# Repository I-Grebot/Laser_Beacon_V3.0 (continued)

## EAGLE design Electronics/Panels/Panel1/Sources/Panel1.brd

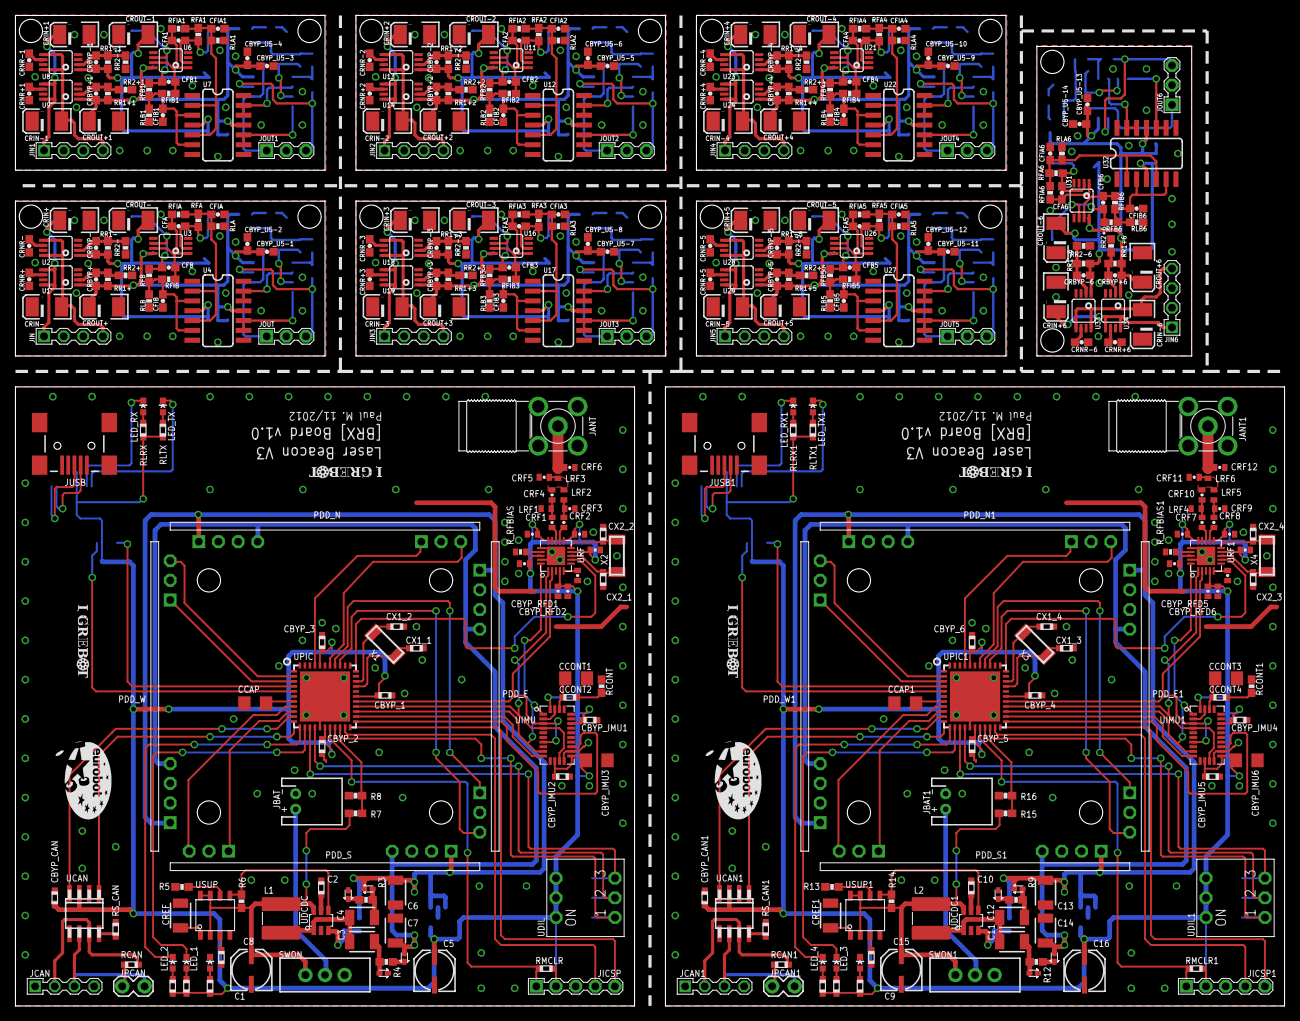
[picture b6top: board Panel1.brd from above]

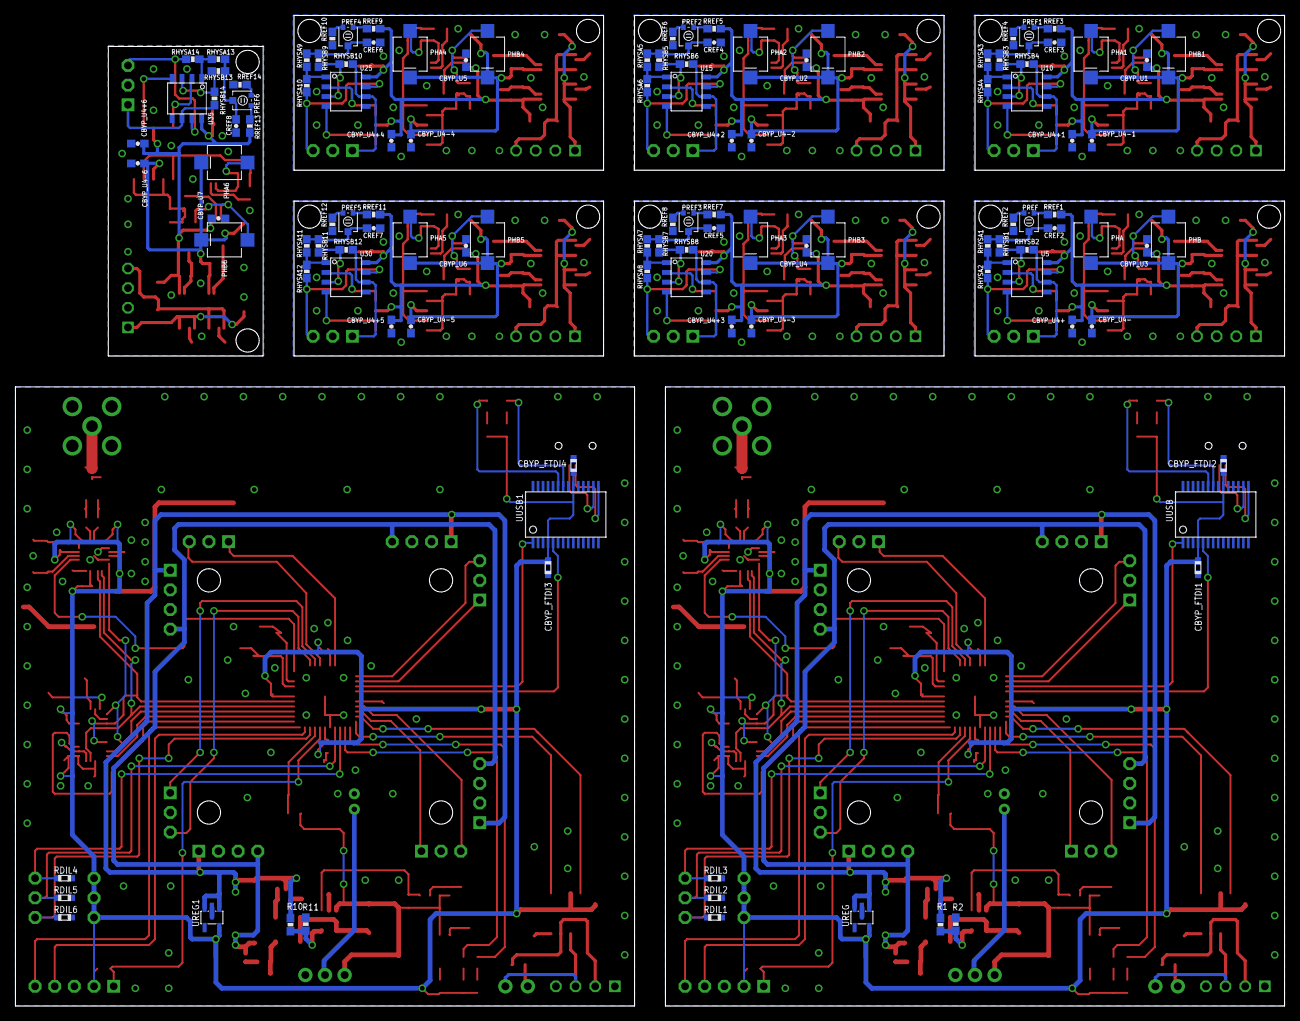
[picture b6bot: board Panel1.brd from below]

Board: 2 copper layers, 164.0 x 128.0 mm, 502 parts (116 on the bottom side), 312 nets.

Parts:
C1, C9: 4.7uF; PANASONIC_C
C2, C10: 47nF_16V; R0603
C3, C4, C11, C12: 1uF_16V; 1210
C5, C16: 10uF; PANASONIC_C
C6, C7, C13, C14: 2.2uF_16V; 1210
C8, C15: 470nF; R0603
CBYP_1, CBYP_2, CBYP_3, CBYP_4, CBYP_5, CBYP_6: 100nF_6.3V; R0603
CBYP_CAN, CBYP_CAN1: 100nF_6.3V; R0603
CBYP_FTDI1, CBYP_FTDI2, CBYP_FTDI3, CBYP_FTDI4: 100nF_6.3V; R0603
CBYP_IMU1, CBYP_IMU2, CBYP_IMU4, CBYP_IMU5: 100nF_6.3V; R0603
CBYP_IMU3, CBYP_IMU6: 10uF_6.3V; 1206
CBYP_RFA1, CBYP_RFA2, CBYP_RFA5, CBYP_RFA6: 100nF_X5R; 0402-CAP
CBYP_RFA3, CBYP_RFA4, CBYP_RFA7, CBYP_RFA8: 220pF_X7R; 0402-CAP
CBYP_RFD1, CBYP_RFD3, CBYP_RFD4, CBYP_RFD5: 100nF_X5R; 0402-CAP
CBYP_RFD2, CBYP_RFD6: 220pF_X7R; 0402-CAP
CBYP_U1, CBYP_U2, CBYP_U3, CBYP_U4, CBYP_U4+, CBYP_U4+1, CBYP_U4+2, CBYP_U4+3, CBYP_U4+4, CBYP_U4+5, CBYP_U4+6, CBYP_U4-, CBYP_U4-1, CBYP_U4-2, CBYP_U4-3, CBYP_U4-4, CBYP_U4-5, CBYP_U4-6, CBYP_U5, CBYP_U5-1, CBYP_U5-3, CBYP_U5-5, CBYP_U5-7, CBYP_U5-9, CBYP_U5-11, CBYP_U5-13, CBYP_U6, CBYP_U7: 1uF; 0603-CAP
CBYP_U5-2, CBYP_U5-4, CBYP_U5-6, CBYP_U5-8, CBYP_U5-10, CBYP_U5-12, CBYP_U5-14: 100nF; 0603-CAP
CCAP, CCAP1: 10uF_6.3V; 1206
CCONT1, CCONT3: 10nF; 1206
CCONT2, CCONT4: 470nF; R0603
CFA, CFA1, CFA2, CFA3, CFA4, CFA5, CFA6: 33pF; 0603-CAP
CFB, CFB1, CFB2, CFB3, CFB4, CFB5, CFB6: 33pF; 0603-CAP
CFIA, CFIA1, CFIA2, CFIA3, CFIA4, CFIA5, CFIA6: 100nF; 0603-CAP
CFIB, CFIB1, CFIB2, CFIB3, CFIB4, CFIB5, CFIB6: 100nF; 0603-CAP
CRBYP+, CRBYP+1, CRBYP+2, CRBYP+3, CRBYP+4, CRBYP+5, CRBYP+6: 10nF; 0603-CAP
CRBYP-, CRBYP-1, CRBYP-2, CRBYP-3, CRBYP-4, CRBYP-5, CRBYP-6: 10nF; 0603-CAP
CREF, CREF1: 1uF; 1210
CREF2, CREF3, CREF4, CREF5, CREF6, CREF7, CREF8: 470nF; 0603-CAP
CRF1, CRF2, CRF7, CRF8: 100pF_NP0; 0402-CAP
CRF3, CRF4, CRF9, CRF10: 1.0pF_NP0; 0402-CAP
CRF5, CRF11: 1.8pF_NP0; 0402-CAP
CRF6, CRF12: 1.5pF_NP0; 0402-CAP
CRIN+, CRIN+1, CRIN+2, CRIN+3, CRIN+4, CRIN+5, CRIN+6: 10uF; EIA3528-KIT
CRIN-, CRIN-1, CRIN-2, CRIN-3, CRIN-4, CRIN-5, CRIN-6: 10uF; EIA3528-KIT
CRNR+, CRNR+1, CRNR+2, CRNR+3, CRNR+4, CRNR+5, CRNR+6: 10nF; 0603-CAP
CRNR-, CRNR-1, CRNR-2, CRNR-3, CRNR-4, CRNR-5, CRNR-6: 10nF; 0603-CAP
CROUT+, CROUT+1, CROUT+2, CROUT+3, CROUT+4, CROUT+5, CROUT+6: 10uF; EIA3528-KIT
CROUT-, CROUT-1, CROUT-2, CROUT-3, CROUT-4, CROUT-5, CROUT-6: 10uF; EIA3528-KIT
CX1_1, CX1_2, CX1_3, CX1_4, CX2_1, CX2_2, CX2_3, CX2_4: 22pF_6.3V; R0603
D1, D2, D3, D4, D5, D6, D7, D8: PMEG2005; SOD-523
JANT, JANT1: ENG_CD_1814400_C1; SMA-PCB-ANGLE
JBAT, JBAT1: JST-2-PTH
JCAN, JCAN1: SIL4; CON4-2.54
JICSP, JICSP1: SIL5; CON5-2.54
JIN, JIN1, JIN2, JIN3, JIN4, JIN5, JIN6: SIL4; CON4-2.54
JOUT, JOUT1, JOUT2, JOUT3, JOUT4, JOUT5, JOUT6: SIL3; CON3-2.54
JPCAN, JPCAN1: 1X02_LOCK
JUSB, JUSB1: USBSMD; USB-MINIB
L1, L2: 10uH; L-5X5
LED_1, LED_2, LED_3, LED_4: LED-0603
LED_POW, LED_POW1: LED-0603
LED_RX, LED_RX1: LED-0603
LED_TX, LED_TX1: LED-0603
LRF1, LRF2, LRF3, LRF4, LRF5, LRF6: 1.2nH; C0402
PDD_E, PDD_E1: PDD_BOARD; PDD_SOCKET
PDD_N, PDD_N1: PDD_BOARD; PDD_SOCKET
PDD_S, PDD_S1: PDD_BOARD; PDD_SOCKET
PDD_W, PDD_W1: PDD_BOARD; PDD_SOCKET
PHA, PHA1, PHA2, PHA3, PHA4, PHA5, PHA6: VBPW34SR
PHB, PHB1, PHB2, PHB3, PHB4, PHB5, PHB6: VBPW34SR
PREF, PREF1, PREF2, PREF3, PREF4, PREF5, PREF6: 100k; TRIM-PVZ2A
R1, R10: 113k; 0603-RES
R2, R11: 13.3k; 0603-RES
R3, R4, R9, R12: 1; 0603-RES
R5, R6, R8, R13, R14, R16: 10k; 0603-RES
R7, R15: 20k; 0603-RES
RCAN, RCAN1: 100; R0603
RCONT, RCONT1: 10k; 0603-RES
RDIL1, RDIL2, RDIL3, RDIL4, RDIL5, RDIL6: 10k; R0603
RFA, RFA1, RFA2, RFA3, RFA4, RFA5, RFA6: 20k; 0603-RES
RFB, RFB1, RFB2, RFB3, RFB4, RFB5, RFB6: 20k; 0603-RES
RFIA, RFIA1, RFIA2, RFIA3, RFIA4, RFIA5, RFIA6: 100; 0603-RES
RFIB, RFIB1, RFIB2, RFIB3, RFIB4, RFIB5, RFIB6: 100; 0603-RES
RHYSA1, RHYSA3, RHYSA5, RHYSA7, RHYSA9, RHYSA11, RHYSA13: 100; 0603-RES
RHYSA2, RHYSA4, RHYSA6, RHYSA8, RHYSA10, RHYSA12, RHYSA14: 10k; 0603-RES
RHYSB1, RHYSB3, RHYSB5, RHYSB7, RHYSB9, RHYSB11, RHYSB13: 100; 0603-RES
RHYSB2, RHYSB4, RHYSB6, RHYSB8, RHYSB10, RHYSB12, RHYSB14: 10k; 0603-RES
RL1, RL2, RL3, RL4: 270; R0603
RLA, RLA1, RLA2, RLA3, RLA4, RLA5, RLA6: 100k; 0603-RES
RLB, RLB1, RLB2, RLB3, RLB4, RLB5, RLB6: 100k; 0603-RES
RLPOW, RLPOW1: 270; R0603
RLRX, RLRX1: 270; R0603
RLTX, RLTX1: 270; R0603
RMCLR, RMCLR1: 4.7k; R0603
RR1+, RR1+1, RR1+2, RR1+3, RR1+4, RR1+5, RR1+6, RR1-, RR1-1, RR1-2, RR1-3, RR1-4, RR1-5, RR1-6: 31.6k; 0603-RES
RR2+, RR2+1, RR2+2, RR2+3, RR2+4, RR2+5, RR2+6, RR2-, RR2-1, RR2-2, RR2-3, RR2-4, RR2-5, RR2-6: 10k; 0603-RES
RREF1, RREF2, RREF3, RREF4, RREF5, RREF6, RREF7, RREF8, RREF9, RREF10, RREF11, RREF12, RREF13, RREF14: 100; 0603-RES
RS_CAN, RS_CAN1: 10k; R0603
R_RFBIAS, R_RFBIAS1: 56k; 0402-RES
SWON, SWON1: SWITCH-SPDT
U1, U9, U14, U19, U24, U29, U34: TPS7A4901NO_PAD; MSOP8
U2, U8, U13, U18, U23, U28, U33: TPS7A3001NO_PAD; MSOP8
U3, U6, U11, U16, U21, U26, U31: OPA2380; MSOP8
U4, U7, U12, U17, U22, U27, U32: INA2143; SOIC14
U5, U10, U15, U20, U25, U30, U35: TLV3502; SOIC8
U$1, U$4, U$5, U$9: LOGOIGREBOT; LOGO_IGREBOT
U$2, U$3: LOGOEUROBOT; LOGO_EUROBOT_1
UCAN, UCAN1: MCP2551; SO-08
UDCDC, UDCDC1: LT3467A; TSOT-23
UDIL, UDIL1: A6E-3104; SW_DIP-3
UIMU, UIMU1: LSM330DL; LLGA-28
UPIC, UPIC1: DSPIC33FJ128MC804_QFN; QFN44-8X8
UREG, UREG1: MCP1801; SOT23-5L
URF, URF1: CC2500; QFN20-0.5
USUP, USUP1: TL7709AC; SOIC8
UUSB, UUSB1: FT232RL-BASICSSOP; SSOP28DB
X1, X3: 8MHz; XTAL_4.9-1.8
X2, X4: 26MHz; XTAL_4.9-1.8

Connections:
3.3V: C5.+, CBYP_1.1, CBYP_2.1, CBYP_3.1, CBYP_CAN.1, CBYP_FTDI1.1, CBYP_FTDI2.1, CBYP_IMU1.1, CBYP_IMU2.1, CBYP_IMU3.1, CBYP_RFA1.2, CBYP_RFA2.2, CBYP_RFA3.2, CBYP_RFA4.2, CBYP_RFD1.2, CBYP_RFD2.2, JICSP.2, RL1.1, RL2.1, RLPOW.1, RLRX.1, RLTX.1, RMCLR.1, UCAN.3, UDIL.1A, UDIL.2A, UDIL.3A, UIMU.12, UIMU.15, UIMU.22, UIMU.28, UPIC.P$17, UPIC.P$28, UPIC.P$40, UREG.5, URF.4, URF.9, URF.11, URF.14, URF.15, URF.18, UUSB.4, UUSB.20
3.3V1: C16.+, CBYP_4.1, CBYP_5.1, CBYP_6.1, CBYP_CAN1.1, CBYP_FTDI3.1, CBYP_FTDI4.1, CBYP_IMU4.1, CBYP_IMU5.1, CBYP_IMU6.1, CBYP_RFA5.2, CBYP_RFA6.2, CBYP_RFA7.2, CBYP_RFA8.2, CBYP_RFD5.2, CBYP_RFD6.2, JICSP1.2, RL3.1, RL4.1, RLPOW1.1, RLRX1.1, RLTX1.1, RMCLR1.1, UCAN1.3, UDIL1.1A, UDIL1.2A, UDIL1.3A, UIMU1.12, UIMU1.15, UIMU1.22, UIMU1.28, UPIC1.P$17, UPIC1.P$28, UPIC1.P$40, UREG1.5, URF1.4, URF1.9, URF1.11, URF1.14, URF1.15, URF1.18, UUSB1.4, UUSB1.20
!CMP_A-B!: JOUT.1, RHYSB2.2, U5.6
!CMP_A-B!1: JOUT1.1, RHYSB4.2, U10.6
!CMP_A-B!2: JOUT2.1, RHYSB6.2, U15.6
!CMP_A-B!3: JOUT3.1, RHYSB8.2, U20.6
!CMP_A-B!4: JOUT4.1, RHYSB10.2, U25.6
!CMP_A-B!5: JOUT5.1, RHYSB12.2, U30.6
!CMP_A-B!6: JOUT6.1, RHYSB14.2, U35.6
!CMP_B-A!: JOUT.3, RHYSA2.2, U5.7
!CMP_B-A!1: JOUT1.3, RHYSA4.2, U10.7
!CMP_B-A!2: JOUT2.3, RHYSA6.2, U15.7
!CMP_B-A!3: JOUT3.3, RHYSA8.2, U20.7
!CMP_B-A!4: JOUT4.3, RHYSA10.2, U25.7
!CMP_B-A!5: JOUT5.3, RHYSA12.2, U30.7
!CMP_B-A!6: JOUT6.3, RHYSA14.2, U35.7
!CSN!_A: UIMU.17, UPIC.P$23
!CSN!_A1: UIMU1.17, UPIC1.P$23
!CSN!_G: UIMU.10, UPIC.P$24
!CSN!_G1: UIMU1.10, UPIC1.P$24
!CSN!_RF: UPIC.P$33, URF.7
!CSN!_RF1: UPIC1.P$33, URF1.7
!MCLR!: JICSP.1, RMCLR.2, UPIC.P$18
!MCLR!1: JICSP1.1, RMCLR1.2, UPIC1.P$18
!SHDN!: R6.2, UDCDC.4, USUP.5
!SHDN!1: R14.2, UDCDC1.4, USUP1.5
+5V: CBYP_U3.1, CBYP_U4+.1, CBYP_U5-1.1, CBYP_U5-2.1, CRBYP+.1, CROUT+.A, RR1+.2, RREF1.1, U1.1, U3.8, U4.11, U5.8
+5V1: CBYP_U1.1, CBYP_U4+1.1, CBYP_U5-3.1, CBYP_U5-4.1, CRBYP+1.1, CROUT+1.A, RR1+1.2, RREF3.1, U6.8, U7.11, U9.1, U10.8
+5V2: CBYP_U2.1, CBYP_U4+2.1, CBYP_U5-5.1, CBYP_U5-6.1, CRBYP+2.1, CROUT+2.A, RR1+2.2, RREF5.1, U11.8, U12.11, U14.1, U15.8
+5V3: CBYP_U4.1, CBYP_U4+3.1, CBYP_U5-7.1, CBYP_U5-8.1, CRBYP+3.1, CROUT+3.A, RR1+3.2, RREF7.1, U16.8, U17.11, U19.1, U20.8
+5V4: CBYP_U4+4.1, CBYP_U5.1, CBYP_U5-9.1, CBYP_U5-10.1, CRBYP+4.1, CROUT+4.A, RR1+4.2, RREF9.1, U21.8, U22.11, U24.1, U25.8
+5V5: CBYP_U4+5.1, CBYP_U5-11.1, CBYP_U5-12.1, CBYP_U6.1, CRBYP+5.1, CROUT+5.A, RR1+5.2, RREF11.1, U26.8, U27.11, U29.1, U30.8
+5V6: CBYP_U4+6.1, CBYP_U5-13.1, CBYP_U5-14.1, CBYP_U7.1, CRBYP+6.1, CROUT+6.A, RR1+6.2, RREF13.1, U31.8, U32.11, U34.1, U35.8
+12V: C6.1, D1.C, PDD_E.1, PDD_N.1, PDD_S.1, PDD_W.1, R1.2, UREG.1, UREG.3
+12V1: C13.1, D5.C, PDD_E1.1, PDD_N1.1, PDD_S1.1, PDD_W1.1, R10.2, UREG1.1, UREG1.3
-5V: CBYP_U4-.2, CRBYP-.1, CROUT-.C, PHA.A, PHB.A, RR1-.2, U2.1, U4.4
-5V1: CBYP_U4-1.2, CRBYP-1.1, CROUT-1.C, PHA1.A, PHB1.A, RR1-1.2, U7.4, U8.1
-5V2: CBYP_U4-2.2, CRBYP-2.1, CROUT-2.C, PHA2.A, PHB2.A, RR1-2.2, U12.4, U13.1
-5V3: CBYP_U4-3.2, CRBYP-3.1, CROUT-3.C, PHA3.A, PHB3.A, RR1-3.2, U17.4, U18.1
-5V4: CBYP_U4-4.2, CRBYP-4.1, CROUT-4.C, PHA4.A, PHB4.A, RR1-4.2, U22.4, U23.1
-5V5: CBYP_U4-5.2, CRBYP-5.1, CROUT-5.C, PHA5.A, PHB5.A, RR1-5.2, U27.4, U28.1
-5V6: CBYP_U4-6.2, CRBYP-6.1, CROUT-6.C, PHA6.A, PHB6.A, RR1-6.2, U32.4, U33.1
-12V: C7.1, D4.A, PDD_E.4, PDD_N.4, PDD_S.4, PDD_W.4
-12V1: C14.1, D8.A, PDD_E1.4, PDD_N1.4, PDD_S1.4, PDD_W1.4
AGND: CBYP_U3.2, CBYP_U4+.2, CBYP_U4-.1, CBYP_U5-1.2, CBYP_U5-2.2, CFIA.2, CFIB.2, CREF2.2, CRIN+.C, CRIN-.A, CRNR+.2, CRNR-.2, CROUT+.C, CROUT-.A, JIN.2, JIN.3, JOUT.2, RLA.1, RLB.1, RR2+.1, RR2-.1, RREF2.1, U1.4, U2.4, U3.3, U3.4, U3.5, U4.8, U4.14, U5.5
AGND1: CBYP_U1.2, CBYP_U4+1.2, CBYP_U4-1.1, CBYP_U5-3.2, CBYP_U5-4.2, CFIA1.2, CFIB1.2, CREF3.2, CRIN+1.C, CRIN-1.A, CRNR+1.2, CRNR-1.2, CROUT+1.C, CROUT-1.A, JIN1.2, JIN1.3, JOUT1.2, RLA1.1, RLB1.1, RR2+1.1, RR2-1.1, RREF4.1, U6.3, U6.4, U6.5, U7.8, U7.14, U8.4, U9.4, U10.5
AGND2: CBYP_U2.2, CBYP_U4+2.2, CBYP_U4-2.1, CBYP_U5-5.2, CBYP_U5-6.2, CFIA2.2, CFIB2.2, CREF4.2, CRIN+2.C, CRIN-2.A, CRNR+2.2, CRNR-2.2, CROUT+2.C, CROUT-2.A, JIN2.2, JIN2.3, JOUT2.2, RLA2.1, RLB2.1, RR2+2.1, RR2-2.1, RREF6.1, U11.3, U11.4, U11.5, U12.8, U12.14, U13.4, U14.4, U15.5
AGND3: CBYP_U4.2, CBYP_U4+3.2, CBYP_U4-3.1, CBYP_U5-7.2, CBYP_U5-8.2, CFIA3.2, CFIB3.2, CREF5.2, CRIN+3.C, CRIN-3.A, CRNR+3.2, CRNR-3.2, CROUT+3.C, CROUT-3.A, JIN3.2, JIN3.3, JOUT3.2, RLA3.1, RLB3.1, RR2+3.1, RR2-3.1, RREF8.1, U16.3, U16.4, U16.5, U17.8, U17.14, U18.4, U19.4, U20.5
AGND4: CBYP_U4+4.2, CBYP_U4-4.1, CBYP_U5.2, CBYP_U5-9.2, CBYP_U5-10.2, CFIA4.2, CFIB4.2, CREF6.2, CRIN+4.C, CRIN-4.A, CRNR+4.2, CRNR-4.2, CROUT+4.C, CROUT-4.A, JIN4.2, JIN4.3, JOUT4.2, RLA4.1, RLB4.1, RR2+4.1, RR2-4.1, RREF10.1, U21.3, U21.4, U21.5, U22.8, U22.14, U23.4, U24.4, U25.5
AGND5: CBYP_U4+5.2, CBYP_U4-5.1, CBYP_U5-11.2, CBYP_U5-12.2, CBYP_U6.2, CFIA5.2, CFIB5.2, CREF7.2, CRIN+5.C, CRIN-5.A, CRNR+5.2, CRNR-5.2, CROUT+5.C, CROUT-5.A, JIN5.2, JIN5.3, JOUT5.2, RLA5.1, RLB5.1, RR2+5.1, RR2-5.1, RREF12.1, U26.3, U26.4, U26.5, U27.8, U27.14, U28.4, U29.4, U30.5
AGND6: CBYP_U4+6.2, CBYP_U4-6.1, CBYP_U5-13.2, CBYP_U5-14.2, CBYP_U7.2, CFIA6.2, CFIB6.2, CREF8.2, CRIN+6.C, CRIN-6.A, CRNR+6.2, CRNR-6.2, CROUT+6.C, CROUT-6.A, JIN6.2, JIN6.3, JOUT6.2, RLA6.1, RLB6.1, RR2+6.1, RR2-6.1, RREF14.1, U31.3, U31.4, U31.5, U32.8, U32.14, U33.4, U34.4, U35.5
CANH: JCAN.2, RCAN.1, UCAN.7
CANH1: JCAN1.2, RCAN1.1, UCAN1.7
CANL: JCAN.3, JPCAN.2, UCAN.6
CANL1: JCAN1.3, JPCAN1.2, UCAN1.6
CAN_RX: UCAN.4, UPIC.P$10
CAN_RX1: UCAN1.4, UPIC1.P$10
CAN_TX: UCAN.1, UPIC.P$11
CAN_TX1: UCAN1.1, UPIC1.P$11
DIL1: RDIL1.1, UDIL.1B, UPIC.P$20
DIL2: RDIL2.1, UDIL.2B, UPIC.P$15
DIL3: RDIL3.1, UDIL.3B, UPIC.P$14
DIL4: RDIL4.1, UDIL1.3B, UPIC1.P$14
DIL5: RDIL5.1, UDIL1.2B, UPIC1.P$15
DIL6: RDIL6.1, UDIL1.1B, UPIC1.P$20
E_!A-B!: PDD_E.5, UPIC.P$37
E_!A-B!1: PDD_E1.5, UPIC1.P$37
E_!B-A!: PDD_E.7, UPIC.P$36
E_!B-A!1: PDD_E1.7, UPIC1.P$36
GND: C1.-, C2.2, C5.-, C6.2, C7.2, C8.2, CBYP_1.2, CBYP_2.2, CBYP_3.2, CBYP_CAN.2, CBYP_FTDI1.2, CBYP_FTDI2.2, CBYP_IMU1.2, CBYP_IMU2.2, CBYP_IMU3.2, CBYP_RFA1.1, CBYP_RFA2.1, CBYP_RFA3.1, CBYP_RFA4.1, CBYP_RFD1.1, CBYP_RFD2.1, CBYP_RFD3.1, CCAP.2, CCONT1.2, CREF.1, CRF3.1, CRF5.1, CRF6.1, CX1_1.2, CX1_2.2, CX2_1.2, CX2_2.2, D2.A, D3.C, JANT.B1, JANT.B2, JANT.B3, JANT.B4, JBAT.1, JCAN.1, JCAN.4, JICSP.3, JUSB.GND, LED_POW.C, LRF1.1, PDD_E.2, PDD_E.3, PDD_E.6, PDD_N.2, PDD_N.3, PDD_N.6, PDD_S.2, PDD_S.3, PDD_S.6, PDD_W.2, PDD_W.3, PDD_W.6, R2.1, R5.1, R8.1, RCONT.1, RDIL1.2, RDIL2.2, RDIL3.2, RS_CAN.1, R_RFBIAS.2, UCAN.2, UDCDC.2, UIMU.2, UIMU.11, UIMU.14, UIMU.16, UIMU.18, UIMU.19, UIMU.20, UIMU.23, UIMU.24, UIMU.25, UIMU.27, UPIC.P$6, UPIC.P$16, UPIC.P$29, UPIC.P$39, UPIC.PAD, UREG.2, URF.16, URF.19, URF.PAD, USUP.4, UUSB.7, UUSB.18, UUSB.21, UUSB.25, UUSB.26
GND1: C9.-, C10.2, C13.2, C14.2, C15.2, C16.-, CBYP_4.2, CBYP_5.2, CBYP_6.2, CBYP_CAN1.2, CBYP_FTDI3.2, CBYP_FTDI4.2, CBYP_IMU4.2, CBYP_IMU5.2, CBYP_IMU6.2, CBYP_RFA5.1, CBYP_RFA6.1, CBYP_RFA7.1, CBYP_RFA8.1, CBYP_RFD4.1, CBYP_RFD5.1, CBYP_RFD6.1, CCAP1.2, CCONT3.2, CREF1.1, CRF9.1, CRF11.1, CRF12.1, CX1_3.2, CX1_4.2, CX2_3.2, CX2_4.2, D6.A, D7.C, JANT1.B1, JANT1.B2, JANT1.B3, JANT1.B4, JBAT1.1, JCAN1.1, JCAN1.4, JICSP1.3, JUSB1.GND, LED_POW1.C, LRF4.1, PDD_E1.2, PDD_E1.3, PDD_E1.6, PDD_N1.2, PDD_N1.3, PDD_N1.6, PDD_S1.2, PDD_S1.3, PDD_S1.6, PDD_W1.2, PDD_W1.3, PDD_W1.6, R11.1, R13.1, R16.1, RCONT1.1, RDIL4.2, RDIL5.2, RDIL6.2, RS_CAN1.1, R_RFBIAS1.2, UCAN1.2, UDCDC1.2, UIMU1.2, UIMU1.11, UIMU1.14, UIMU1.16, UIMU1.18, UIMU1.19, UIMU1.20, UIMU1.23, UIMU1.24, UIMU1.25, UIMU1.27, UPIC1.P$6, UPIC1.P$16, UPIC1.P$29, UPIC1.P$39, UPIC1.PAD, UREG1.2, URF1.16, URF1.19, URF1.PAD, USUP1.4, UUSB1.7, UUSB1.18, UUSB1.21, UUSB1.25, UUSB1.26
LED_1: LED_1.C, UPIC.P$13
LED_2: LED_2.C, UPIC.P$12
LED_3: LED_3.C, UPIC1.P$13
LED_4: LED_4.C, UPIC1.P$12
LED_RX: LED_RX.C, UUSB.22
LED_RX1: LED_RX1.C, UUSB1.22
LED_TX: LED_TX.C, UUSB.23
LED_TX1: LED_TX1.C, UUSB1.23
MISO: UIMU.3, UIMU.7, UPIC.P$27, URF.2
MISO1: UIMU1.3, UIMU1.7, UPIC1.P$27, URF1.2
MOSI: UIMU.1, UIMU.9, UPIC.P$25, URF.20
MOSI1: UIMU1.1, UIMU1.9, UPIC1.P$25, URF1.20
unnamed: CRF1.2, CRF4.2, LRF1.2
unnamed: LED_TX.A, RLTX.2
unnamed: CRF2.2, CRF3.2, LRF2.1
unnamed: CRF4.1, CRF5.2, LRF2.2, LRF3.1
unnamed: RS_CAN.2, UCAN.8
unnamed: JPCAN.1, RCAN.2
unnamed: CRF6.2, JANT.A, LRF3.2
unnamed: LED_RX.A, RLRX.2
unnamed: LED_1.A, RL1.2
unnamed: LED_2.A, RL2.2
unnamed: C2.1, UDCDC.5
unnamed: JBAT.2, SWON.2
unnamed: C3.1, C4.1, L1.2, UDCDC.1
unnamed: C3.2, D3.A, R4.2
unnamed: D2.C, R3.1
unnamed: C4.2, D1.A, R3.2
unnamed: R5.2, USUP.6
unnamed: R1.1, R2.2, UDCDC.3
unnamed: D4.C, R4.1
unnamed: CCONT2.2, RCONT.2
unnamed: LED_POW.A, RLPOW.2
unnamed: RS_CAN1.2, UCAN1.8
unnamed: CRF7.2, CRF10.2, LRF4.2
unnamed: CRF8.2, CRF9.2, LRF5.1
unnamed: CRF10.1, CRF11.2, LRF5.2, LRF6.1
unnamed: CRF12.2, JANT1.A, LRF6.2
unnamed: JPCAN1.1, RCAN1.2
unnamed: LED_TX1.A, RLTX1.2
unnamed: LED_RX1.A, RLRX1.2
unnamed: LED_3.A, RL3.2
unnamed: LED_4.A, RL4.2
unnamed: C11.1, C12.1, L2.2, UDCDC1.1
unnamed: C10.1, UDCDC1.5
unnamed: D6.C, R9.1
unnamed: C12.2, D5.A, R9.2
unnamed: D8.C, R12.1
unnamed: C11.2, D7.A, R12.2
unnamed: R10.1, R11.2, UDCDC1.3
unnamed: R13.2, USUP1.6
unnamed: JBAT1.2, SWON1.2
unnamed: CCONT4.2, RCONT1.2
unnamed: LED_POW1.A, RLPOW1.2
unnamed: CRNR+.1, U1.6
unnamed: CRNR-.1, U2.6
unnamed: CRBYP+.2, RR1+.1, RR2+.2, U1.2
unnamed: CRBYP-.2, RR1-.1, RR2-.2, U2.2
unnamed: CFA.2, RFIA.1, U3.1
unnamed: CFA.1, PHA.K, RFA.1, U3.2
unnamed: CFB.2, RFIB.1, U3.7
unnamed: CFB.1, PHB.K, RFB.1, U3.6
unnamed: RHYSA1.2, RHYSA2.1, U5.1
unnamed: RHYSB1.2, RHYSB2.1, U5.3
unnamed: PREF.1, RREF1.2
unnamed: PREF.3, RREF2.2
unnamed: CRNR+1.1, U9.6
unnamed: CRNR-1.1, U8.6
unnamed: CRBYP+1.2, RR1+1.1, RR2+1.2, U9.2
unnamed: CRBYP-1.2, RR1-1.1, RR2-1.2, U8.2
unnamed: CFA1.2, RFIA1.1, U6.1
unnamed: CFA1.1, PHA1.K, RFA1.1, U6.2
unnamed: CFB1.2, RFIB1.1, U6.7
unnamed: CFB1.1, PHB1.K, RFB1.1, U6.6
unnamed: RHYSA3.2, RHYSA4.1, U10.1
unnamed: RHYSB3.2, RHYSB4.1, U10.3
unnamed: PREF1.1, RREF3.2
unnamed: PREF1.3, RREF4.2
unnamed: CRNR+2.1, U14.6
unnamed: CRNR-2.1, U13.6
unnamed: CRBYP+2.2, RR1+2.1, RR2+2.2, U14.2
unnamed: CRBYP-2.2, RR1-2.1, RR2-2.2, U13.2
unnamed: CFA2.2, RFIA2.1, U11.1
unnamed: CFA2.1, PHA2.K, RFA2.1, U11.2
unnamed: CFB2.2, RFIB2.1, U11.7
unnamed: CFB2.1, PHB2.K, RFB2.1, U11.6
unnamed: RHYSA5.2, RHYSA6.1, U15.1
unnamed: RHYSB5.2, RHYSB6.1, U15.3
unnamed: PREF2.1, RREF5.2
unnamed: PREF2.3, RREF6.2
unnamed: CRNR+3.1, U19.6
unnamed: CRNR-3.1, U18.6
unnamed: CRBYP+3.2, RR1+3.1, RR2+3.2, U19.2
unnamed: CRBYP-3.2, RR1-3.1, RR2-3.2, U18.2
unnamed: CFA3.2, RFIA3.1, U16.1
unnamed: CFA3.1, PHA3.K, RFA3.1, U16.2
unnamed: CFB3.2, RFIB3.1, U16.7
unnamed: CFB3.1, PHB3.K, RFB3.1, U16.6
unnamed: RHYSA7.2, RHYSA8.1, U20.1
unnamed: RHYSB7.2, RHYSB8.1, U20.3
unnamed: PREF3.1, RREF7.2
unnamed: PREF3.3, RREF8.2
unnamed: CRNR+4.1, U24.6
unnamed: CRNR-4.1, U23.6
unnamed: CRBYP+4.2, RR1+4.1, RR2+4.2, U24.2
unnamed: CRBYP-4.2, RR1-4.1, RR2-4.2, U23.2
unnamed: CFA4.2, RFIA4.1, U21.1
unnamed: CFA4.1, PHA4.K, RFA4.1, U21.2
unnamed: CFB4.2, RFIB4.1, U21.7
unnamed: CFB4.1, PHB4.K, RFB4.1, U21.6
unnamed: RHYSA9.2, RHYSA10.1, U25.1
unnamed: RHYSB9.2, RHYSB10.1, U25.3
unnamed: PREF4.1, RREF9.2
unnamed: PREF4.3, RREF10.2
unnamed: CRNR+5.1, U29.6
unnamed: CRNR-5.1, U28.6
unnamed: CRBYP+5.2, RR1+5.1, RR2+5.2, U29.2
unnamed: CRBYP-5.2, RR1-5.1, RR2-5.2, U28.2
unnamed: CFA5.2, RFIA5.1, U26.1
unnamed: CFA5.1, PHA5.K, RFA5.1, U26.2
unnamed: CFB5.2, RFIB5.1, U26.7
unnamed: CFB5.1, PHB5.K, RFB5.1, U26.6
unnamed: RHYSA11.2, RHYSA12.1, U30.1
unnamed: RHYSB11.2, RHYSB12.1, U30.3
unnamed: PREF5.1, RREF11.2
unnamed: PREF5.3, RREF12.2
unnamed: CRNR+6.1, U34.6
unnamed: CRNR-6.1, U33.6
unnamed: CRBYP+6.2, RR1+6.1, RR2+6.2, U34.2
unnamed: CRBYP-6.2, RR1-6.1, RR2-6.2, U33.2
unnamed: CFA6.2, RFIA6.1, U31.1
unnamed: CFA6.1, PHA6.K, RFA6.1, U31.2
unnamed: CFB6.2, RFIB6.1, U31.7
unnamed: CFB6.1, PHB6.K, RFB6.1, U31.6
unnamed: RHYSA13.2, RHYSA14.1, U35.1
unnamed: RHYSB13.2, RHYSB14.1, U35.3
unnamed: PREF6.1, RREF13.2
unnamed: PREF6.3, RREF14.2
N_!A-B!: PDD_N.5, UPIC.P$41
N_!A-B!1: PDD_N1.5, UPIC1.P$41
N_!B-A!: PDD_N.7, UPIC.P$38
N_!B-A!1: PDD_N1.7, UPIC1.P$38
PGC: JICSP.5, UPIC.P$22
PGC1: JICSP1.5, UPIC1.P$22
PGD: JICSP.4, UPIC.P$21
PGD1: JICSP1.4, UPIC1.P$21
RF_N: CRF1.1, URF.13
RF_N1: CRF7.1, URF1.13
RF_P: CRF2.1, URF.12
RF_P1: CRF8.1, URF1.12
R_RFBIAS: R_RFBIAS.1, URF.17
R_RFBIAS1: R_RFBIAS1.1, URF1.17
SCLK: UIMU.4, UIMU.13, UPIC.P$26, URF.1
SCLK1: UIMU1.4, UIMU1.13, UPIC1.P$26, URF1.1
SENSE_BAT: R7.2, R8.2, UPIC.P$19
SENSE_BAT1: R15.2, R16.2, UPIC1.P$19
SUB_A-B: U4.9, U4.10, U5.4
SUB_A-B1: U7.9, U7.10, U10.4
SUB_A-B2: U12.9, U12.10, U15.4
SUB_A-B3: U17.9, U17.10, U20.4
SUB_A-B4: U22.9, U22.10, U25.4
SUB_A-B5: U27.9, U27.10, U30.4
SUB_A-B6: U32.9, U32.10, U35.4
SUB_B-A: U4.12, U4.13, U5.2
SUB_B-A1: U7.12, U7.13, U10.2
SUB_B-A2: U12.12, U12.13, U15.2
SUB_B-A3: U17.12, U17.13, U20.2
SUB_B-A4: U22.12, U22.13, U25.2
SUB_B-A5: U27.12, U27.13, U30.2
SUB_B-A6: U32.12, U32.13, U35.2
S_!A-B!: PDD_S.5, UPIC.P$9
S_!A-B!1: PDD_S1.5, UPIC1.P$9
S_!B-A!: PDD_S.7, UPIC.P$8
S_!B-A!1: PDD_S1.7, UPIC1.P$8
TI_A: CFIA.1, RFA.2, RFIA.2, RLA.2, U4.2, U4.5
TI_A1: CFIA1.1, RFA1.2, RFIA1.2, RLA1.2, U7.2, U7.5
TI_A2: CFIA2.1, RFA2.2, RFIA2.2, RLA2.2, U12.2, U12.5
TI_A3: CFIA3.1, RFA3.2, RFIA3.2, RLA3.2, U17.2, U17.5
TI_A4: CFIA4.1, RFA4.2, RFIA4.2, RLA4.2, U22.2, U22.5
TI_A5: CFIA5.1, RFA5.2, RFIA5.2, RLA5.2, U27.2, U27.5
TI_A6: CFIA6.1, RFA6.2, RFIA6.2, RLA6.2, U32.2, U32.5
TI_B: CFIB.1, RFB.2, RFIB.2, RLB.2, U4.3, U4.6
TI_B1: CFIB1.1, RFB1.2, RFIB1.2, RLB1.2, U7.3, U7.6
TI_B2: CFIB2.1, RFB2.2, RFIB2.2, RLB2.2, U12.3, U12.6
TI_B3: CFIB3.1, RFB3.2, RFIB3.2, RLB3.2, U17.3, U17.6
TI_B4: CFIB4.1, RFB4.2, RFIB4.2, RLB4.2, U22.3, U22.6
TI_B5: CFIB5.1, RFB5.2, RFIB5.2, RLB5.2, U27.3, U27.6
TI_B6: CFIB6.1, RFB6.2, RFIB6.2, RLB6.2, U32.3, U32.6
USBDM: JUSB.D-, UUSB.16
USBDM1: JUSB1.D-, UUSB1.16
USBDP: JUSB.D+, UUSB.15
USBDP1: JUSB1.D+, UUSB1.15
USB_RX: UPIC.P$5, UUSB.5
USB_RX1: UPIC1.P$5, UUSB1.5
USB_TX: UPIC.P$4, UUSB.1
USB_TX1: UPIC1.P$4, UUSB1.1
VBAT: C1.+, L1.1, R6.1, R7.1, SWON.1, UDCDC.6, USUP.2, USUP.7, USUP.8
VBAT1: C9.+, L2.1, R14.1, R15.1, SWON1.1, UDCDC1.6, USUP1.2, USUP1.7, USUP1.8
VCAP: CCAP.1, UPIC.P$7
VCAP1: CCAP1.1, UPIC1.P$7
VCONT: CCONT1.1, CCONT2.1, UIMU.26
VCONT1: CCONT3.1, CCONT4.1, UIMU1.26
VCT: C8.1, USUP.3
VCT1: C15.1, USUP1.3
VDCOUPL: CBYP_RFD3.2, URF.5
VDCOUPL1: CBYP_RFD4.2, URF1.5
VIN+: CRIN+.A, JIN.1, U1.5, U1.8
VIN+1: CRIN+1.A, JIN1.1, U9.5, U9.8
VIN+2: CRIN+2.A, JIN2.1, U14.5, U14.8
VIN+3: CRIN+3.A, JIN3.1, U19.5, U19.8
VIN+4: CRIN+4.A, JIN4.1, U24.5, U24.8
VIN+5: CRIN+5.A, JIN5.1, U29.5, U29.8
VIN+6: CRIN+6.A, JIN6.1, U34.5, U34.8
VIN-: CRIN-.C, JIN.4, U2.5, U2.8
VIN-1: CRIN-1.C, JIN1.4, U8.5, U8.8
VIN-2: CRIN-2.C, JIN2.4, U13.5, U13.8
VIN-3: CRIN-3.C, JIN3.4, U18.5, U18.8
VIN-4: CRIN-4.C, JIN4.4, U23.5, U23.8
VIN-5: CRIN-5.C, JIN5.4, U28.5, U28.8
VIN-6: CRIN-6.C, JIN6.4, U33.5, U33.8
VREF: CREF.2, USUP.1
VREF1: CREF1.2, USUP1.1
VREF2: CREF2.1, PREF.2, RHYSA1.1, RHYSB1.1
VREF3: CREF3.1, PREF1.2, RHYSA3.1, RHYSB3.1
VREF4: CREF4.1, PREF2.2, RHYSA5.1, RHYSB5.1
VREF5: CREF5.1, PREF3.2, RHYSA7.1, RHYSB7.1
VREF6: CREF6.1, PREF4.2, RHYSA9.1, RHYSB9.1
VREF7: CREF7.1, PREF5.2, RHYSA11.1, RHYSB11.1
VREF8: CREF8.1, PREF6.2, RHYSA13.1, RHYSB13.1
W_!A-B!: PDD_W.5, UPIC.P$3
W_!A-B!1: PDD_W1.5, UPIC1.P$3
W_!B-A!: PDD_W.7, UPIC.P$2
W_!B-A!1: PDD_W1.7, UPIC1.P$2
X1_OSC1: CX1_1.1, UPIC.P$30, X1.P$1
X1_OSC2: CX1_2.1, UPIC.P$31, X1.P$2
X1_OSC3: CX1_3.1, UPIC1.P$30, X3.P$1
X1_OSC4: CX1_4.1, UPIC1.P$31, X3.P$2
X2_OSC1: CX2_1.1, URF.8, X2.P$1
X2_OSC2: CX2_2.1, URF.10, X2.P$2
X2_OSC3: CX2_3.1, URF1.8, X4.P$1
X2_OSC4: CX2_4.1, URF1.10, X4.P$2

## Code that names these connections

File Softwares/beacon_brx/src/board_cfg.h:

/* -----------------------------------------------------------------------------
 * Beacon [BRX]
 * I-Grebot Laser Beacon V3.0
 * -----------------------------------------------------------------------------
 * File        : board_cfg.h
 * Language    : C
 * Author      : Paul M.
 * Creation    : 2013-03-10
 * -----------------------------------------------------------------------------
 * Description
 *   See main module header file for a full description
 * -----------------------------------------------------------------------------
 * Versionning informations
 * Repository: http://svn2.assembla.com/svn/paranoid_android/
 * -----------------------------------------------------------------------------
 * $Rev:: 877                                                                  $
 * $LastChangedBy:: Paul.M                                                     $
 * $LastChangedDate:: 2013-03-30 23:59:51 +0100 (sam., 30 mars 2013)           $
 * -----------------------------------------------------------------------------
 * Version     Comment                                   Author       Date
 * 1.0         Initial release                           Paul M.      2013-03-10
 * -----------------------------------------------------------------------------
 */

#ifndef _BOARD_H_
#define _BOARD_H_

// Hardware main include
#include <p33Fxxxx.h>

// Compiler related types
typedef unsigned char uint8_t ;
typedef signed   char sint8_t ;
typedef unsigned int  uint16_t;
typedef signed   int  sint16_t;
typedef unsigned long uint32_t;
typedef signed   long sint32_t;

// -----------------------------------------------------------------------------
// FREQUENCIES
// -----------------------------------------------------------------------------

// Primary Oscillator frequency
#define FIN 8000000

// FOSC = (FIN/N1) * M / N2
// N1 = 4, M = 32, N2 = 2
#define PLL_RATIO (32/(4*2))

// Add-up all frequency tunnings
#define FOSC 64000000 // (FIN*PLL_RATIO)
#define FCY  32000000 // (FOSC/2)

#define NCY_FOR_ONE_MS 50000 // rough estimate for 1ms active delay

// -----------------------------------------------------------------------------
// PPS IO MACROS
// -----------------------------------------------------------------------------

#define UNLOCK_PPS {__builtin_write_OSCCONL(OSCCON & 0xBF); \
                    while(OSCCONbits.IOLOCK);  }
#define LOCK_PPS   {__builtin_write_OSCCONL(OSCCON | 0x40); \
                    while(!OSCCONbits.IOLOCK); }

// -----------------------------------------------------------------------------
// HARDWARE
// -----------------------------------------------------------------------------

/*
 * Remainder for Peripheral Pin Selection
 *
 * RB0 to RB15 => RP0 to RP15
 * RC0 to RC9  => RP16 to RP25
 */

// SPI RF Interfaces //TODO rename because we use multiple SPI
// --------------

// CSN_A output mapped on RB2/RP2
#define CSN_A_TRIS    (TRISBbits.TRISB2)
#define CSN_A         (PORTBbits.RB2)

// CSN_G output mapped on RB3/RP3
#define CSN_G_TRIS    (TRISBbits.TRISB3)
#define CSN_G         (PORTBbits.RB3)

// CSN_RF output mapped on RB4/RP4
#define CSN_RF_TRIS   (TRISBbits.TRISB4)
#define CSN_RF        (PORTBbits.RB4)

// SCK output mapped on RC1/RP17
#define SCK_TRIS      (TRISCbits.TRISC1)
#define SCK_RPN       (RPOR8bits.RP17R)

// MOSI output mapped on RC0/RP16
#define MOSI_TRIS     (TRISCbits.TRISC0)
#define MOSI_RPN      (RPOR8bits.RP16R)

// MISO input mapped on RC2/RP18
#define MISO_TRIS     (TRISCbits.TRISC2)
#define MISO_PIN       18

// PDD Boards interface
// --------------------

// N_B-A input mapped on RB5/RP5
#define PDD_N_BA_TRIS      (TRISBbits.TRISB5)
#define PDD_N_BA_PIN        5

// N_A-B input mapped on RC5/RP21
#define PDD_N_AB_TRIS      (TRISCbits.TRISC5)
#define PDD_N_AB_PIN        21

// E_B-A input mapped on RC3/RP19
#define PDD_E_BA_TRIS      (TRISCbits.TRISC3)
#define PDD_E_BA_PIN        19

// E_A-B input mapped on RC4/RP20
#define PDD_E_AB_TRIS      (TRISCbits.TRISC4)
#define PDD_E_AB_PIN        20

// S_B-A input mapped on RB10/RP10
#define PDD_S_BA_TRIS      (TRISBbits.TRISB10)
#define PDD_S_BA_PIN        10

// S_A-B input mapped on RB11/RP11
#define PDD_S_AB_TRIS      (TRISBbits.TRISB11)
#define PDD_S_AB_PIN        11

// W_B-A input mapped on RC6/RP22
#define PDD_W_BA_TRIS      (TRISCbits.TRISC6)
#define PDD_W_BA_PIN        22

// W_A-B input mapped on RC7/RP23
#define PDD_W_AB_TRIS      (TRISCbits.TRISC7)
#define PDD_W_AB_PIN        23

// DIL Switchs
// -----------

// DIL_1 input mapped on RA1
#define DIL_1_TRIS    (TRISAbits.TRISA1)
#define DIL_1         (PORTAbits.RA1)

// DIL_2 input mapped on RB15
#define DIL_2_TRIS    (TRISBbits.TRISB15)
#define DIL_2         (PORTBbits.RB15)

// DIL_3 input mapped on RB14
#define DIL_3_TRIS    (TRISBbits.TRISB14)
#define DIL_3         (PORTBbits.RB14)

// LEDs
// ----

// LED_1 output mapped on RA7
#define LED_1_TRIS (TRISAbits.TRISA7)
#define LED_1      (PORTAbits.RA7)

// LED_2 output mapped on RA10
#define LED_2_TRIS (TRISAbits.TRISA10)
#define LED_2      (PORTAbits.RA10)

// UART Interface
// --------------

// UART_TX output mapped on RC9/RP25
#define UART_TX_TRIS  (TRISCbits.TRISC9)
#define UART_TX_RPN   (RPOR12bits.RP25R)

// UART_RX input mapped on RC8/RP24
#define UART_RX_TRIS  (TRISCbits.TRISC8)
#define UART_RX_PIN   24

// -----------------------------------------------------------------------------
// CC2500 LIBRARY SETUP
// -----------------------------------------------------------------------------

// CC2500 uses SPI1
#undef CC2500_USE_SPI2

// Define I/Os tristate registers
#define CC2500_SS_TRIS  CSN_RF_TRIS
#define CC2500_SCK_TRIS SCK_TRIS
#define CC2500_SDO_TRIS MOSI_TRIS
#define CC2500_SDI_TRIS MISO_TRIS

// Define I/Os remappable registers & values
#define CC2500_SCK_RPN SCK_RPN
#define CC2500_SDO_RPN MOSI_RPN
#define CC2500_SDI_PIN MISO_PIN

// Define I/Os ports
#define CC2500_SS  CSN_RF

// -----------------------------------------------------------------------------
// BEACON SYSTEM LIBRARY SETUP
// -----------------------------------------------------------------------------

// Indicate that the board is slave
#undef BEACON_COM_IS_MASTER
//#define BEACON_COM_IS_MASTER

// Define the DIL switchs
#define BEACON_COM_DIL_B2_TRIS DIL_1_TRIS // DIL_1 is MSB
#define BEACON_COM_DIL_B1_TRIS DIL_2_TRIS
#define BEACON_COM_DIL_B0_TRIS DIL_3_TRIS // DIL_3 is LSB

#define BEACON_COM_DIL_B2 DIL_1
#define BEACON_COM_DIL_B1 DIL_2
#define BEACON_COM_DIL_B0 DIL_3

// -----------------------------------------------------------------------------
// PDD BOARDS SETUP
// -----------------------------------------------------------------------------

// N_B-A detection mapped on IC1
#define PDD_N_BA_RPN (RPINR7bits.IC1R)

// E_B-A detection mapped on IC2
#define PDD_E_BA_RPN (RPINR7bits.IC2R)

// S_B-A detection mapped on IC7
#define PDD_S_BA_RPN (RPINR10bits.IC7R)

// W_B-A detection mapped on IC8
#define PDD_W_BA_RPN (RPINR10bits.IC8R)

// -----------------------------------------------------------------------------
// DEBUG SETUP
// -----------------------------------------------------------------------------

#define DEBUG_UART_RX_TRIS UART_RX_TRIS
#define DEBUG_UART_RX_PIN  UART_RX_PIN
#define DEBUG_UART_TX_TRIS UART_TX_TRIS
#define DEBUG_UART_TX_RPN  UART_TX_RPN

// Using UART1
#define DEBUG_UART_TX_PIN 0b00011
#define DEBUG_UART_RX_RPN (RPINR18bits.U1RXR)

#endif

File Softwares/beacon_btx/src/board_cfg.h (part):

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
// TOP Feedback input mapped on RB2/RP2/C1IN-
#define DRUM_TOP_TRIS       (TRISBbits.TRISB2)
#define DRUM_TOP            (CMCONbits.C1OUT)

// TUD Power modulation
// --------------------
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
// RF_CSN output mapped on RB13/RP13
#define RF_CSN_TRIS   (TRISBbits.TRISB13)
#define RF_CSN (PORTBbits.RB13)

// RF_SCLK output mapped on RB11/RP11
#define RF_SCK_TRIS   (TRISBbits.TRISB11)
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
// RF_MISO input mapped on RB12/RP12
#define RF_MISO_TRIS  (TRISBbits.TRISB12)
#define RF_MISO_PIN   12


// SPI beacon slave Interfaces
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
// CAN_RX input mapped on RB6/RP6
#define CAN_RX_TRIS  (TRISBbits.TRISB6)
#define CAN_RX_PIN   6

// CAN_TX mapped on RB5/RP5
#define CAN_TX_TRIS  (TRISBbits.TRISB5)
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
// UART_RX input mapped on RC3/RP19
#define UART_RX_TRIS  (TRISCbits.TRISC3)
#define UART_RX_PIN   19

// LEDs
// ----

// LED_1 output mapped on RA7
#define LED_1_TRIS (TRISAbits.TRISA7)
#define LED_1      (PORTAbits.RA7)

// LED_2 output mapped on RA10
#define LED_2_TRIS (TRISAbits.TRISA10)
#define LED_2      (PORTAbits.RA10)

// Spare I/Os
// ----------
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
// CAN uses ECAN1
#define ECAN1_RX_TRIS  CAN_RX_TRIS
#define ECAN1_RX_PIN   CAN_RX_PIN
#define ECAN1_TX_TRIS  CAN_TX_TRIS
#define ECAN1_TX_RPN   CAN_TX_RPN

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// Define I/Os remappable registers & values
#define CC2500_SCK_RPN RF_SCK_RPN
#define CC2500_SDO_RPN RF_MOSI_RPN
#define CC2500_SDI_PIN RF_MISO_PIN

// Define I/Os ports
#define CC2500_SS  RF_CSN

// -----------------------------------------------------------------------------
// BEACON SYSTEM LIBRARY SETUP
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#define LED_GREEN_TRIS LED_1_TRIS
#define LED_RED_TRIS   LED_2_TRIS

#define LED_GREEN LED_1
#define LED_RED   LED_2

// -----------------------------------------------------------------------------
// DEBUG SETUP
// -----------------------------------------------------------------------------

#define DEBUG_UART_RX_TRIS UART_RX_TRIS
#define DEBUG_UART_RX_PIN  UART_RX_PIN
#define DEBUG_UART_TX_TRIS UART_TX_TRIS
#define DEBUG_UART_TX_RPN  UART_TX_RPN

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
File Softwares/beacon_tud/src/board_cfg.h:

/* -----------------------------------------------------------------------------
 * Beacon [TUD]
 * I-Grebot Laser Beacon V3.0
 * -----------------------------------------------------------------------------
 * File        : board_cfg.h
 * Language    : C
 * Author      : Paul M.
 * Creation    : 2013-01-13
 * -----------------------------------------------------------------------------
 * Description
 *   See main module header file for a full description
 * -----------------------------------------------------------------------------
 * Versionning informations
 * Repository: http://svn2.assembla.com/svn/paranoid_android/
 * -----------------------------------------------------------------------------
 * $Rev:: 836                                                                  $
 * $LastChangedBy:: Paul.M                                                     $
 * $LastChangedDate:: 2013-01-13 17:43:44 +0100 (dim., 13 janv. 2013)          $
 * -----------------------------------------------------------------------------
 * Version     Comment                                   Author       Date
 * 1.0         Initial release                           Paul M.      2013-01-13
 * -----------------------------------------------------------------------------
 */

#ifndef _BOARD_CFG_H
#define _BOARD_CFG_H

#ifdef USE_HITECH_CC

// Using HI-TECH PIC Compiler main header
#include <htc.h>

// Fore reference only, not meant to be included directly
#ifndef	_HTC_H_
    #include <pic16f1825.h>
#endif

#endif // !USE_HITECH_CC

// Compiler related types
typedef unsigned char uint8_t;
typedef signed   char sint8_t;
typedef unsigned int uint16_t;
typedef signed   int sint16_t;

// -----------------------------------------------------------------------------
// FREQUENCIES
// -----------------------------------------------------------------------------

// Oscilator frequency
#define F_OSC 32000000 // Do not use the word fOSC which is a configuration bit!

// -----------------------------------------------------------------------------
// HARDWARE
// -----------------------------------------------------------------------------

// UART for commands RX input
// --------------------------

#define UART_RX_TRIS (TRISCbits.TRISC5)
#define UART_RX      (LATCbits.LATC5)

// Laser power
// -----------

#define LASER_ON_TRIS (TRISAbits.TRISA5)
#define LASER_ON      (LATAbits.LATA5)

// LEDs for POV
// ------------

#define LED_7_TRIS (TRISAbits.TRISA4)
#define LED_7      (LATAbits.LATA4)

#define LED_6_TRIS (TRISCbits.TRISC4)
#define LED_6      (LATCbits.LATC4)

#define LED_5_TRIS (TRISCbits.TRISC3)
#define LED_5      (LATCbits.LATC3)

#define LED_4_TRIS (TRISCbits.TRISC2)
#define LED_4      (LATCbits.LATC2)

#define LED_3_TRIS (TRISCbits.TRISC1)
#define LED_3      (LATCbits.LATC1)

#define LED_2_TRIS (TRISCbits.TRISC0)
#define LED_2      (LATCbits.LATC0)

#define LED_1_TRIS (TRISAbits.TRISA2)
#define LED_1      (LATAbits.LATA2)

#endif // ! _BOARD_CFG_H

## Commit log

2016-11-03 Porting from assembla to Git
    First porting gathering everything related to laser Beacon V3
2016-11-04 Add watchdog
    Add mission lib - watchdog.c
2016-11-04 make buildable, remove unneeded project file, update project to MplabX with XC8 and XC16 compiler
2017-01-17 working BTX
2017-04-02 WIP before computer change
2017-04-23 all calculation validated on Python
2017-05-06 work in progress SPI
2017-05-08 XY position of main robot seems to work embedded
2017-05-08 full positionning to be tested
2017-05-14 SPI working, main needed registers can be read
2017-05-17 Opponent Mechanical Milling
2017-05-17 add the arduino SPI master used for validation
